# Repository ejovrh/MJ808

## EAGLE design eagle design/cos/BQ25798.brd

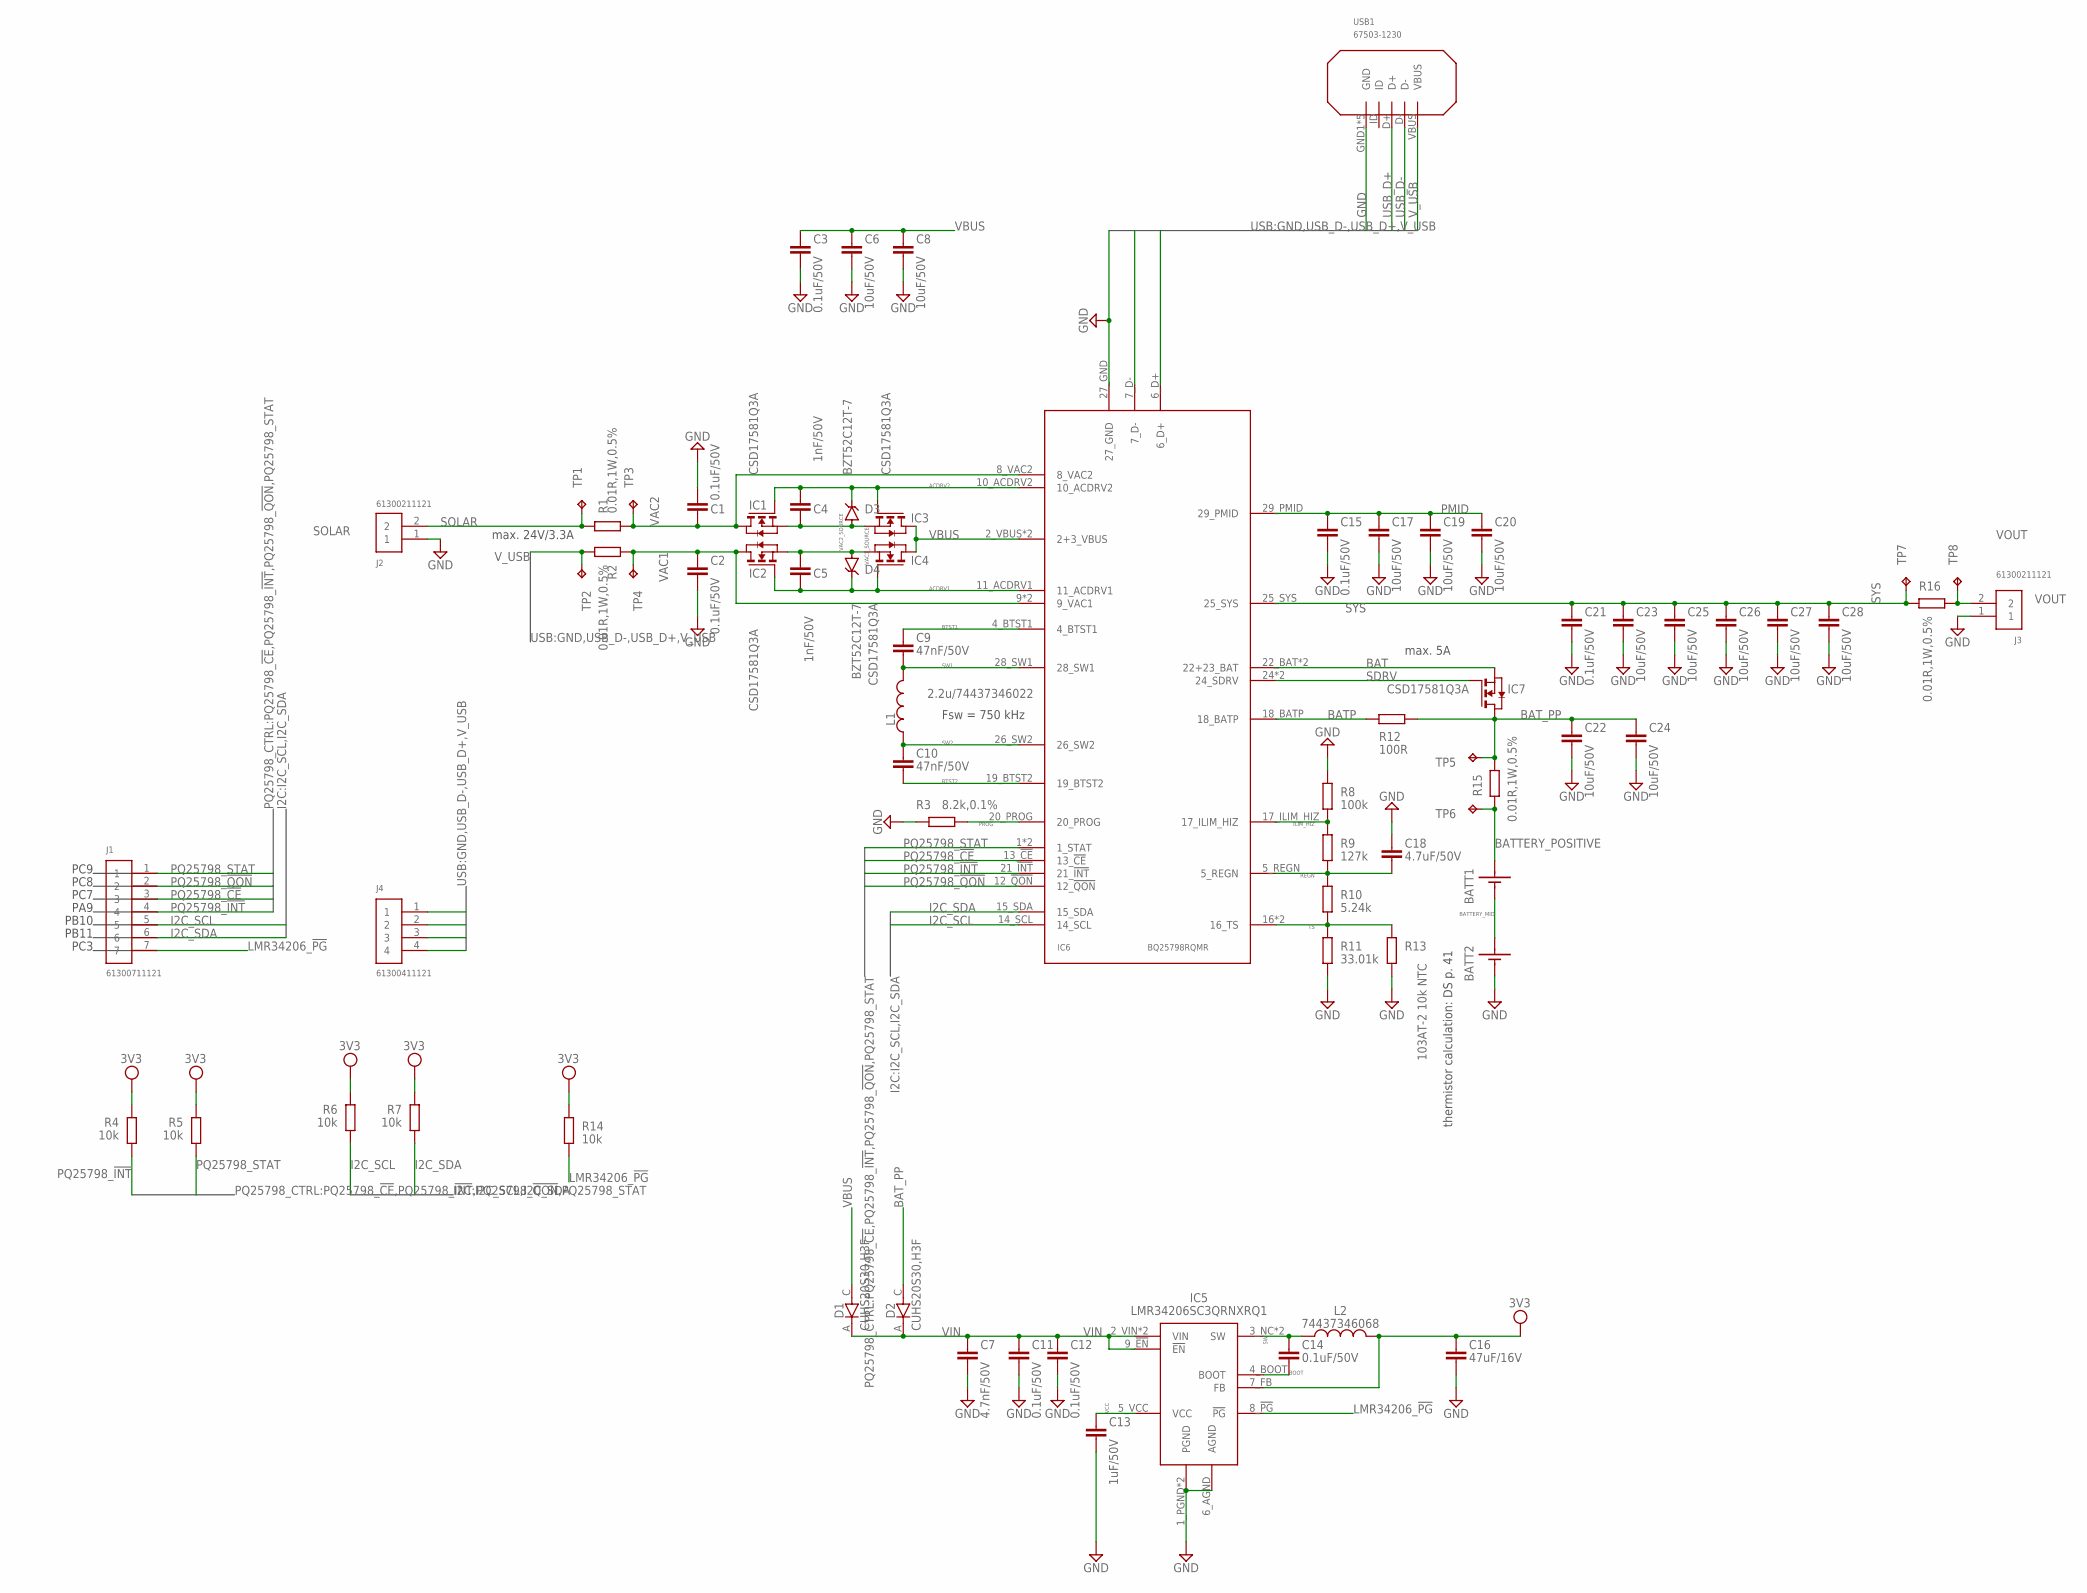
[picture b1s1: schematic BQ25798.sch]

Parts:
BATT1, BATT2: BATTERY; TH
C1, C2, C3, C11, C12, C14, C15, C21: 0.1uF/50V; C0402
C4, C5: 1nF/50V; C0402
C6, C8, C17, C19, C20, C22, C23, C24, C25, C26, C27, C28: 10uF/50V; C0805
C7: 4.7nF/50V; C0805
C9, C10: 47nF/50V; C0603
C13: 1uF/50V; C0805
C16: 47uF/16V; C1206
C18: 4.7uF/50V; C0603
D1, D2: CUHS20S30,H3F; US2H
D3, D4: BZT52C12T-7; SOD-523-2
IC1, IC2, IC3, IC4, IC7: CSD17581Q3A; PQFN-12
IC5: LMR34206SC3QRNXRQ1; VQFN-HR(12)
IC6: BQ25798RQMR; QFN29
J1: 61300711121
J2, J3: 61300211121
J4: 61300411121
L1: 2.2u/74437346022; SMD
L2: 74437346068; SMD
R1, R2, R15, R16: 0.01R,1W,0.5%; R1206
R3: 8.2k,0.1%; R0603; MOUSER 667-ERJ-PB6B8201V
R4, R5, R6, R7, R14: 10k; R0402
R8: 100k; R0402
R9: 127k; R0402
R10: 5.24k; R0402
R11: 33.01k; R0402
R12: 100R; R0603
R13: 103AT-2 10k NTC; V526-0
TP1, TP2, TP3, TP4, TP5, TP6, TP7, TP8: TPPAD1-13; P1-13
USB1: 67503-1230; SMT

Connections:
3V3: C16.1, IC5.7_FB (FB), L2.P$2, R4.2, R5.2, R6.2, R7.2, R14.1
ACDRV1: C5.2, D4.C, IC2.4_G (G), IC4.4_G (G), IC6.11_ACDRV1
ACDRV2: C4.1, D3.C, IC1.4_G (G), IC3.4_G (G), IC6.10_ACDRV2
BAT: IC6.22_BAT (22+23_BAT), IC6.23_BAT (22+23_BAT), IC7.1_S (S), IC7.2_S (S), IC7.3_S (S)
BATP: IC6.18_BATP, R12.1
BATTERY_MID: BATT1.- (NEG), BATT2.+ (POS)
BATTERY_POSITIVE: BATT1.+ (POS), R15.1, TP6.TP
BAT_PP: C22.1, C24.1, D2.C, IC7.5_D (D), IC7.6_D (D), IC7.7_D (D), IC7.8_D (D), IC7.9_D (D), R12.2, R15.2, TP5.TP
BOOT: C14.2, IC5.4_BOOT (BOOT)
BTST1: C9.1, IC6.4_BTST1
BTST2: C10.2, IC6.19_BTST2
GND: BATT2.- (NEG), C1.1, C2.2, C3.2, C6.2, C7.2, C8.2, C11.2, C12.2, C13.2, C15.2, C16.2, C17.2, C18.1, C19.2, C20.2, C21.2, C22.2, C23.2, C24.2, C25.2, C26.2, C27.2, C28.2, IC5.1_PGND (PGND), IC5.6_AGND (AGND), IC5.11_PGND (PGND), IC6.27_GND, J2.1, J3.1, J4.1, R3.1, R8.1, R11.2, R13.2, USB1.GND1 (GND), USB1.GND2 (GND), USB1.GND3 (GND), USB1.GND4 (GND), USB1.GND5 (GND)
I2C_SCL: IC6.14_SCL, J1.5, R6.1
I2C_SDA: IC6.15_SDA, J1.6, R7.1
ILIM_HIZ: IC6.17_ILIM_HIZ, R8.2, R9.1
LMR34206_!PG!: IC5.8_!PG! (!PG!), J1.7, R14.2
PMID: C15.1, C17.1, C19.1, C20.1, IC6.29_PMID
PQ25798_!CE!: IC6.13_!CE!, J1.3
PQ25798_!INT!: IC6.21_!INT!, J1.4, R4.1
PQ25798_!QON!: IC6.12_!QON!, J1.2
PQ25798_STAT: IC6.1 (1_STAT), IC6.1_STAT, J1.1, R5.1
PROG: IC6.20_PROG, R3.2
REGN: C18.2, IC6.5_REGN, R9.2, R10.1
SDRV: IC6.24 (24_SDRV), IC6.24_SDRV, IC7.4_G (G)
SOLAR: J2.2, R1.1, TP1.TP
SW: C14.1, IC5.3_NC (SW), IC5.12_SW (SW), L2.P$1
SW1: C9.2, IC6.28_SW1, L1.P$2
SW2: C10.1, IC6.26_SW2, L1.P$1
SYS: C21.1, C23.1, C25.1, C26.1, C27.1, C28.1, IC6.25_SYS, R16.1, TP7.TP
TS: IC6.16 (16_TS), IC6.16_TS, R10.2, R11.1, R13.1
USB_D+: IC6.6_D+, J4.2, USB1.D+
USB_D-: IC6.7_D-, J4.3, USB1.D-
VAC1: C2.1, IC2.5_D (D), IC2.6_D (D), IC2.7_D (D), IC2.8_D (D), IC2.9_D (D), IC6.9 (9_VAC1), IC6.9_VAC1, R2.2, TP4.TP
VAC1_SOURCE: C5.1, D4.A, IC2.1_S (S), IC2.2_S (S), IC2.3_S (S), IC4.1_S (S), IC4.2_S (S), IC4.3_S (S)
VAC2: C1.2, IC1.5_D (D), IC1.6_D (D), IC1.7_D (D), IC1.8_D (D), IC1.9_D (D), IC6.8_VAC2, R1.2, TP3.TP
VAC2_SOURCE: C4.2, D3.A, IC1.1_S (S), IC1.2_S (S), IC1.3_S (S), IC3.1_S (S), IC3.2_S (S), IC3.3_S (S)
VBUS: C3.1, C6.1, C8.1, D1.C, IC3.5_D (D), IC3.6_D (D), IC3.7_D (D), IC3.8_D (D), IC3.9_D (D), IC4.5_D (D), IC4.6_D (D), IC4.7_D (D), IC4.8_D (D), IC4.9_D (D), IC6.2_VBUS (2+3_VBUS), IC6.3_VBUS (2+3_VBUS)
VCC: C13.1, IC5.5_VCC (VCC)
VIN: C7.1, C11.1, C12.1, D1.A, D2.A, IC5.2_VIN (VIN), IC5.9_!EN! (!EN!), IC5.10_VIN (VIN)
VOUT: J3.2, R16.2, TP8.TP
V_USB: J4.4, R2.1, TP2.TP, USB1.VBUS

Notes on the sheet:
max. 24V/3.3A
max. 5A
Fsw = 750 kHz
thermistor calculation: DS p. 41
PB11
PC9
PC8
PA9
PC7
PC3
PB10

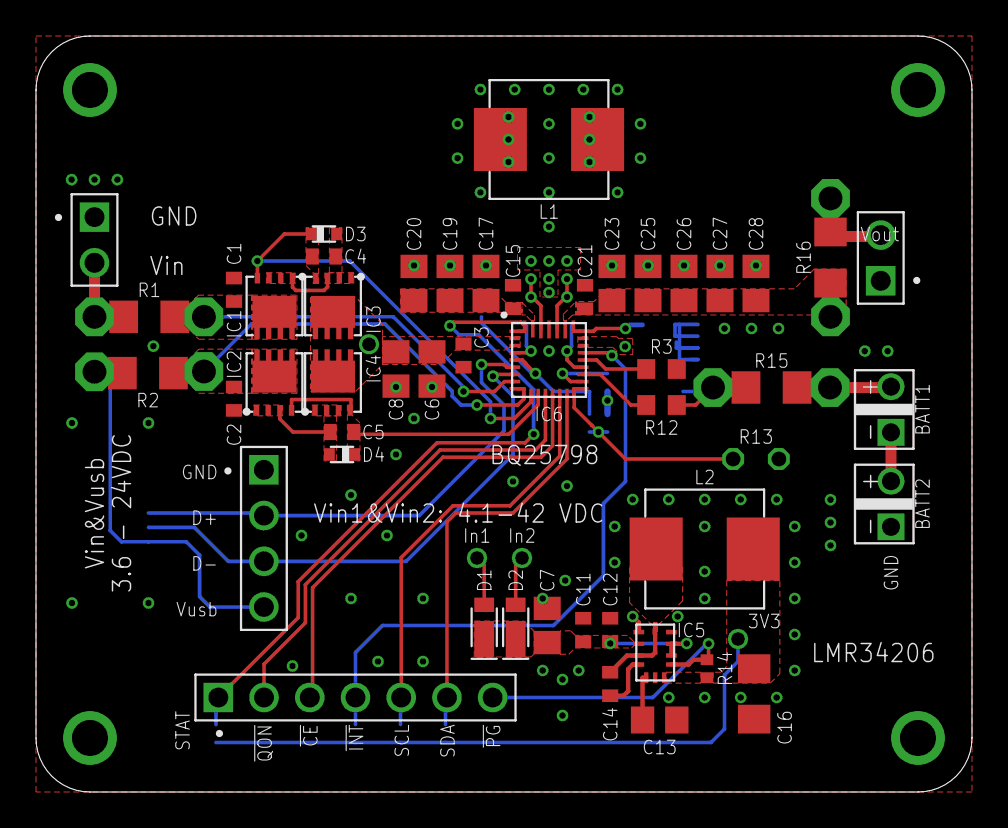
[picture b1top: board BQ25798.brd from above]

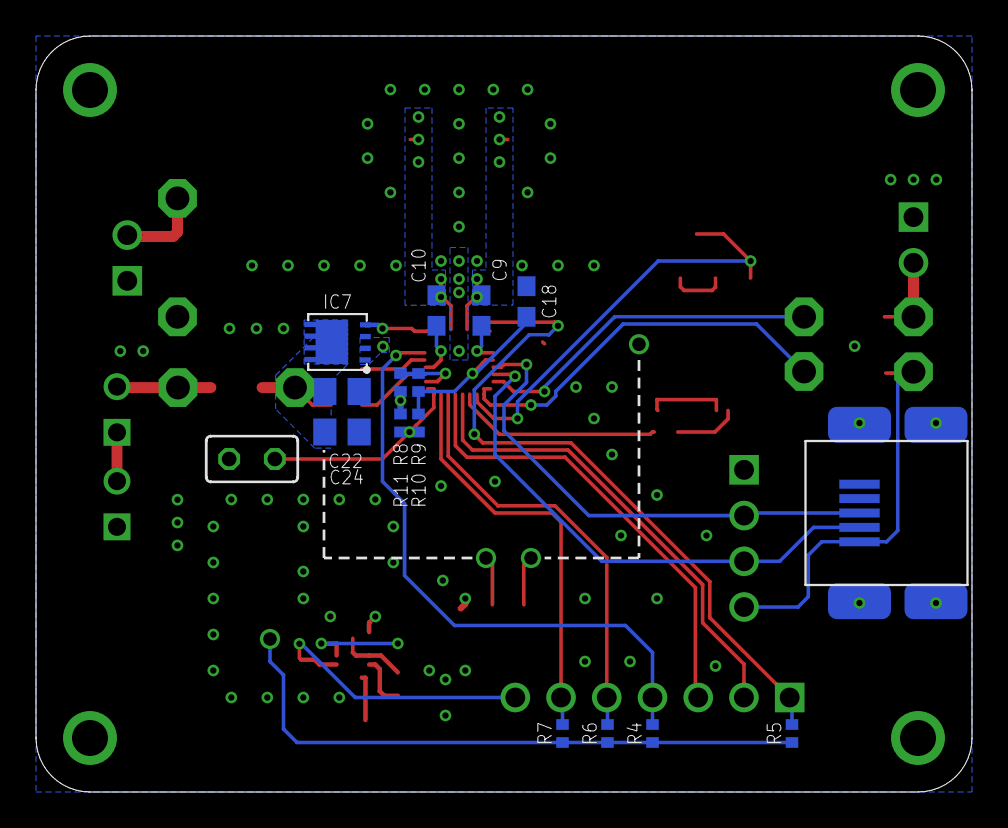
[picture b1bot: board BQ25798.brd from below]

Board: 2 copper layers, 52.0 x 42.0 mm, 72 parts (16 on the bottom side), 41 nets.

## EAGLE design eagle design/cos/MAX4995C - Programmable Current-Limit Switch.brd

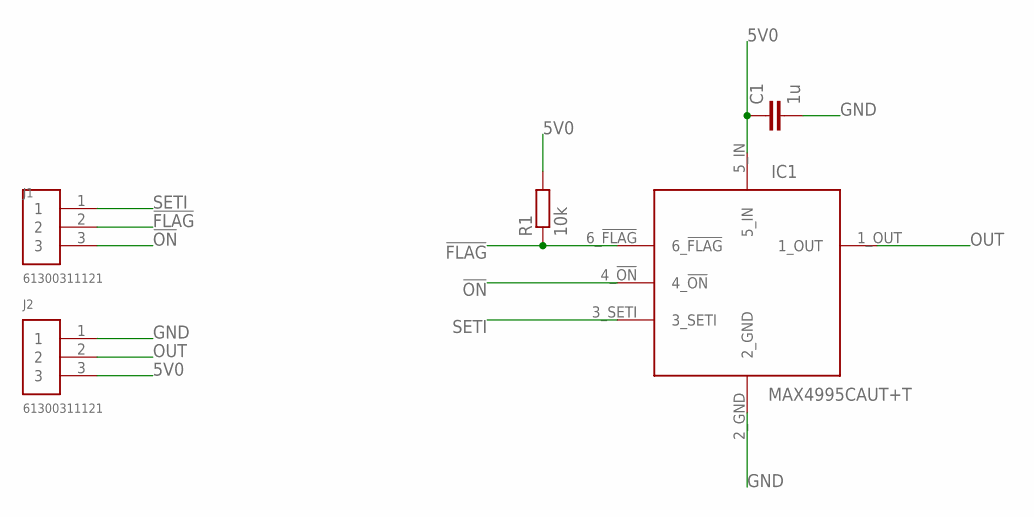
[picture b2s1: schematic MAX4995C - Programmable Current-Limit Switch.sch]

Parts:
C1: 1u; C0805
IC1: MAX4995CAUT+T; SOT23-6
J1, J2: 61300311121
R1: 10k; R0805

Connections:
5V0: C1.1, IC1.5_IN, J2.3, R1.2
!FLAG!: IC1.6_!FLAG!, J1.2, R1.1
!ON!: IC1.4_!ON!, J1.3
GND: C1.2, IC1.2_GND, J2.1
OUT: IC1.1_OUT, J2.2
SETI: IC1.3_SETI, J1.1

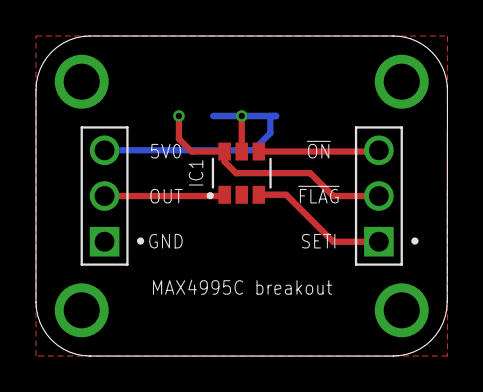
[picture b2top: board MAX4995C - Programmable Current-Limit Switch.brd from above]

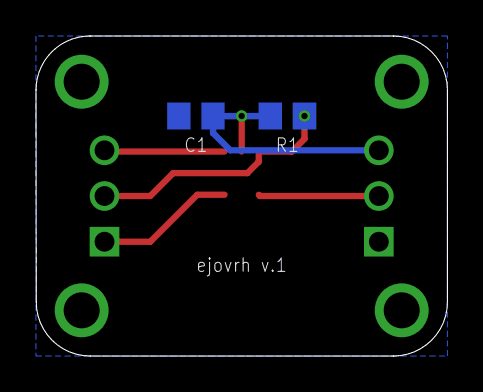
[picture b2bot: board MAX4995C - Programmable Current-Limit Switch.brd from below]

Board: 2 copper layers, 22.9 x 17.8 mm, 5 parts (2 on the bottom side), 6 nets.

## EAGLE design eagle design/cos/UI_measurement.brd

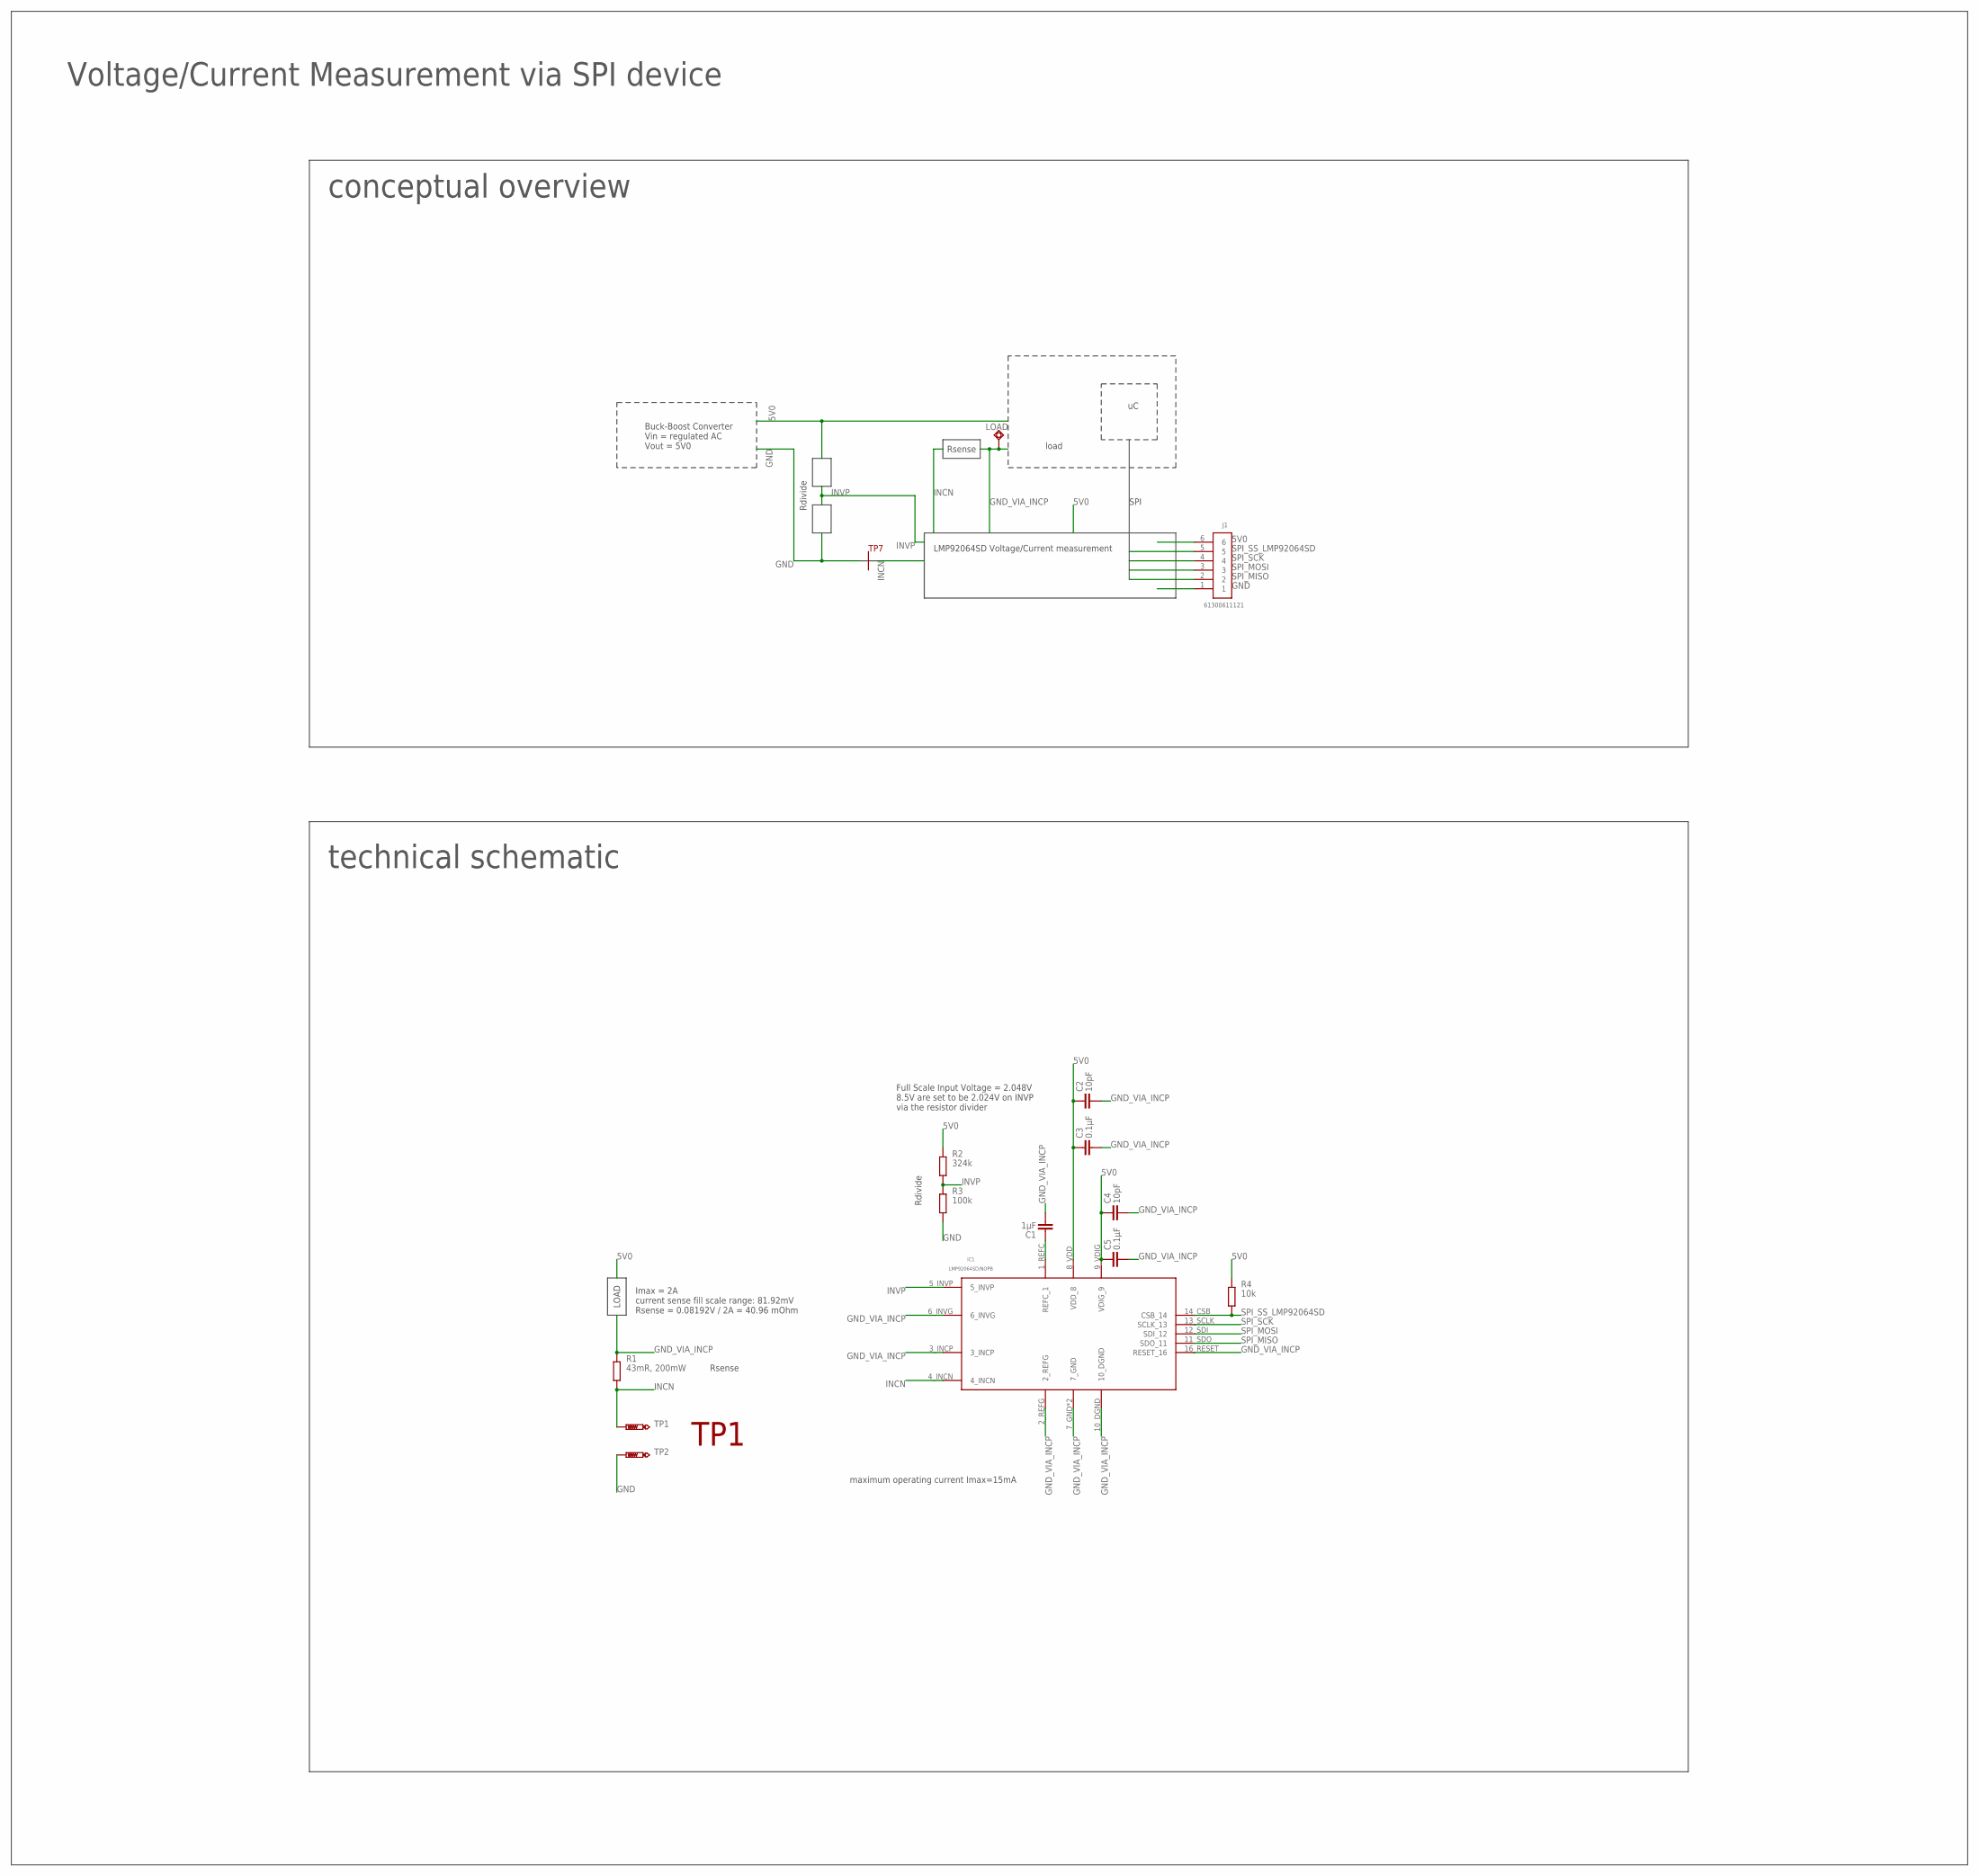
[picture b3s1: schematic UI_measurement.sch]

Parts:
C1: 1μF; C0402
C2, C4: 10pF; C0402
C3, C5: 0.1μF; C0402
IC1: LMP92064SD/NOPB; WSON-16
J1: 61300611121
LOAD: TPSQPAD1-13; P1-13
R1: 43mR, 200mW; R2512
R2: 324k; R0402
R3: 100k; R0402
R4: 10k; R0402
TP1, TP2: PTR1TP10SQ; TP10SQ

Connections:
5V0: C2.1, C3.1, C4.1, C5.1, IC1.8_VDD (VDD_8), IC1.9_VDIG (VDIG_9), J1.6, R2.2, R4.2
GND: J1.1, R3.1, TP2.TP
GND_VIA_INCP: C1.2, C2.2, C3.2, C4.2, C5.2, IC1.2_REFG, IC1.3_INCP, IC1.6_INVG, IC1.7_GND, IC1.10_DGND, IC1.16_RESET (RESET_16), IC1.GND1 (7_GND), LOAD.TP, R1.2
INCN: IC1.4_INCN, R1.1, TP1.TP
INVP: IC1.5_INVP, R2.1, R3.2
unnamed: C1.1, IC1.1_REFC (REFC_1)
SPI_MISO: IC1.11_SDO (SDO_11), J1.2
SPI_MOSI: IC1.12_SDI (SDI_12), J1.3
SPI_SCK: IC1.13_SCLK (SCLK_13), J1.4
SPI_SS_LMP92064SD: IC1.14_CSB (CSB_14), J1.5, R4.1

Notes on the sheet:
Voltage/Current Measurement via SPI device
Buck-Boost Converter Vin = regulated AC Vout = 5V0
conceptual overview
technical schematic
Full Scale Input Voltage = 2.048V 8.5V are set to be 2.024V on INVP via the resistor divider
maximum operating current Imax=15mA
Rsense
Rdivide
LOAD
TP1
TP7
Imax = 2A current sense fill scale range: 81.92mV Rsense = 0.08192V / 2A = 40.96 mOhm
LMP92064SD Voltage/Current measurement
SPI
load

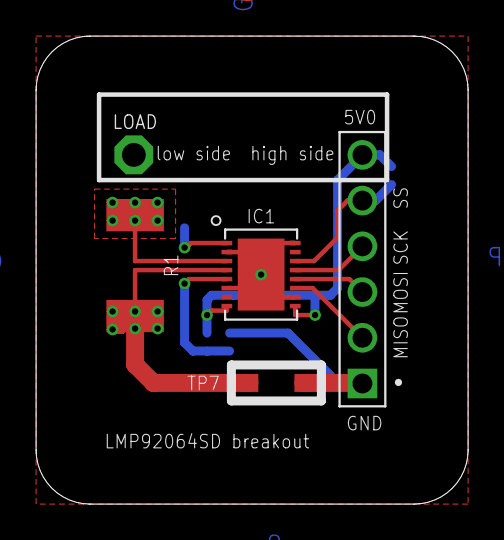
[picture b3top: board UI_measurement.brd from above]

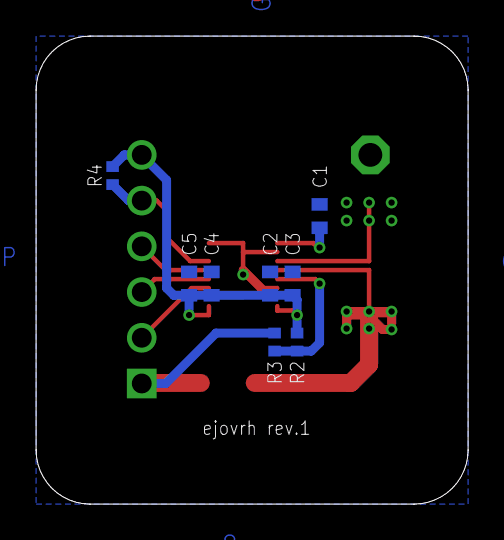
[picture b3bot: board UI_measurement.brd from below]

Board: 2 copper layers, 24.0 x 26.0 mm, 14 parts (8 on the bottom side), 10 nets.
